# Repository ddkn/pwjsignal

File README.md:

# PWJSignal Daughter Board

This is the daughter board to the [pwjrtos](https://github.com/nanomagneticslab/pwjrtos)
OS. This was built using KiCAD v5.1.5.

These are design files for the PCB; this includes,

* Schematics
* PCB layouts
* Gerbers (for PCB manufacturers)
* Datasheet references

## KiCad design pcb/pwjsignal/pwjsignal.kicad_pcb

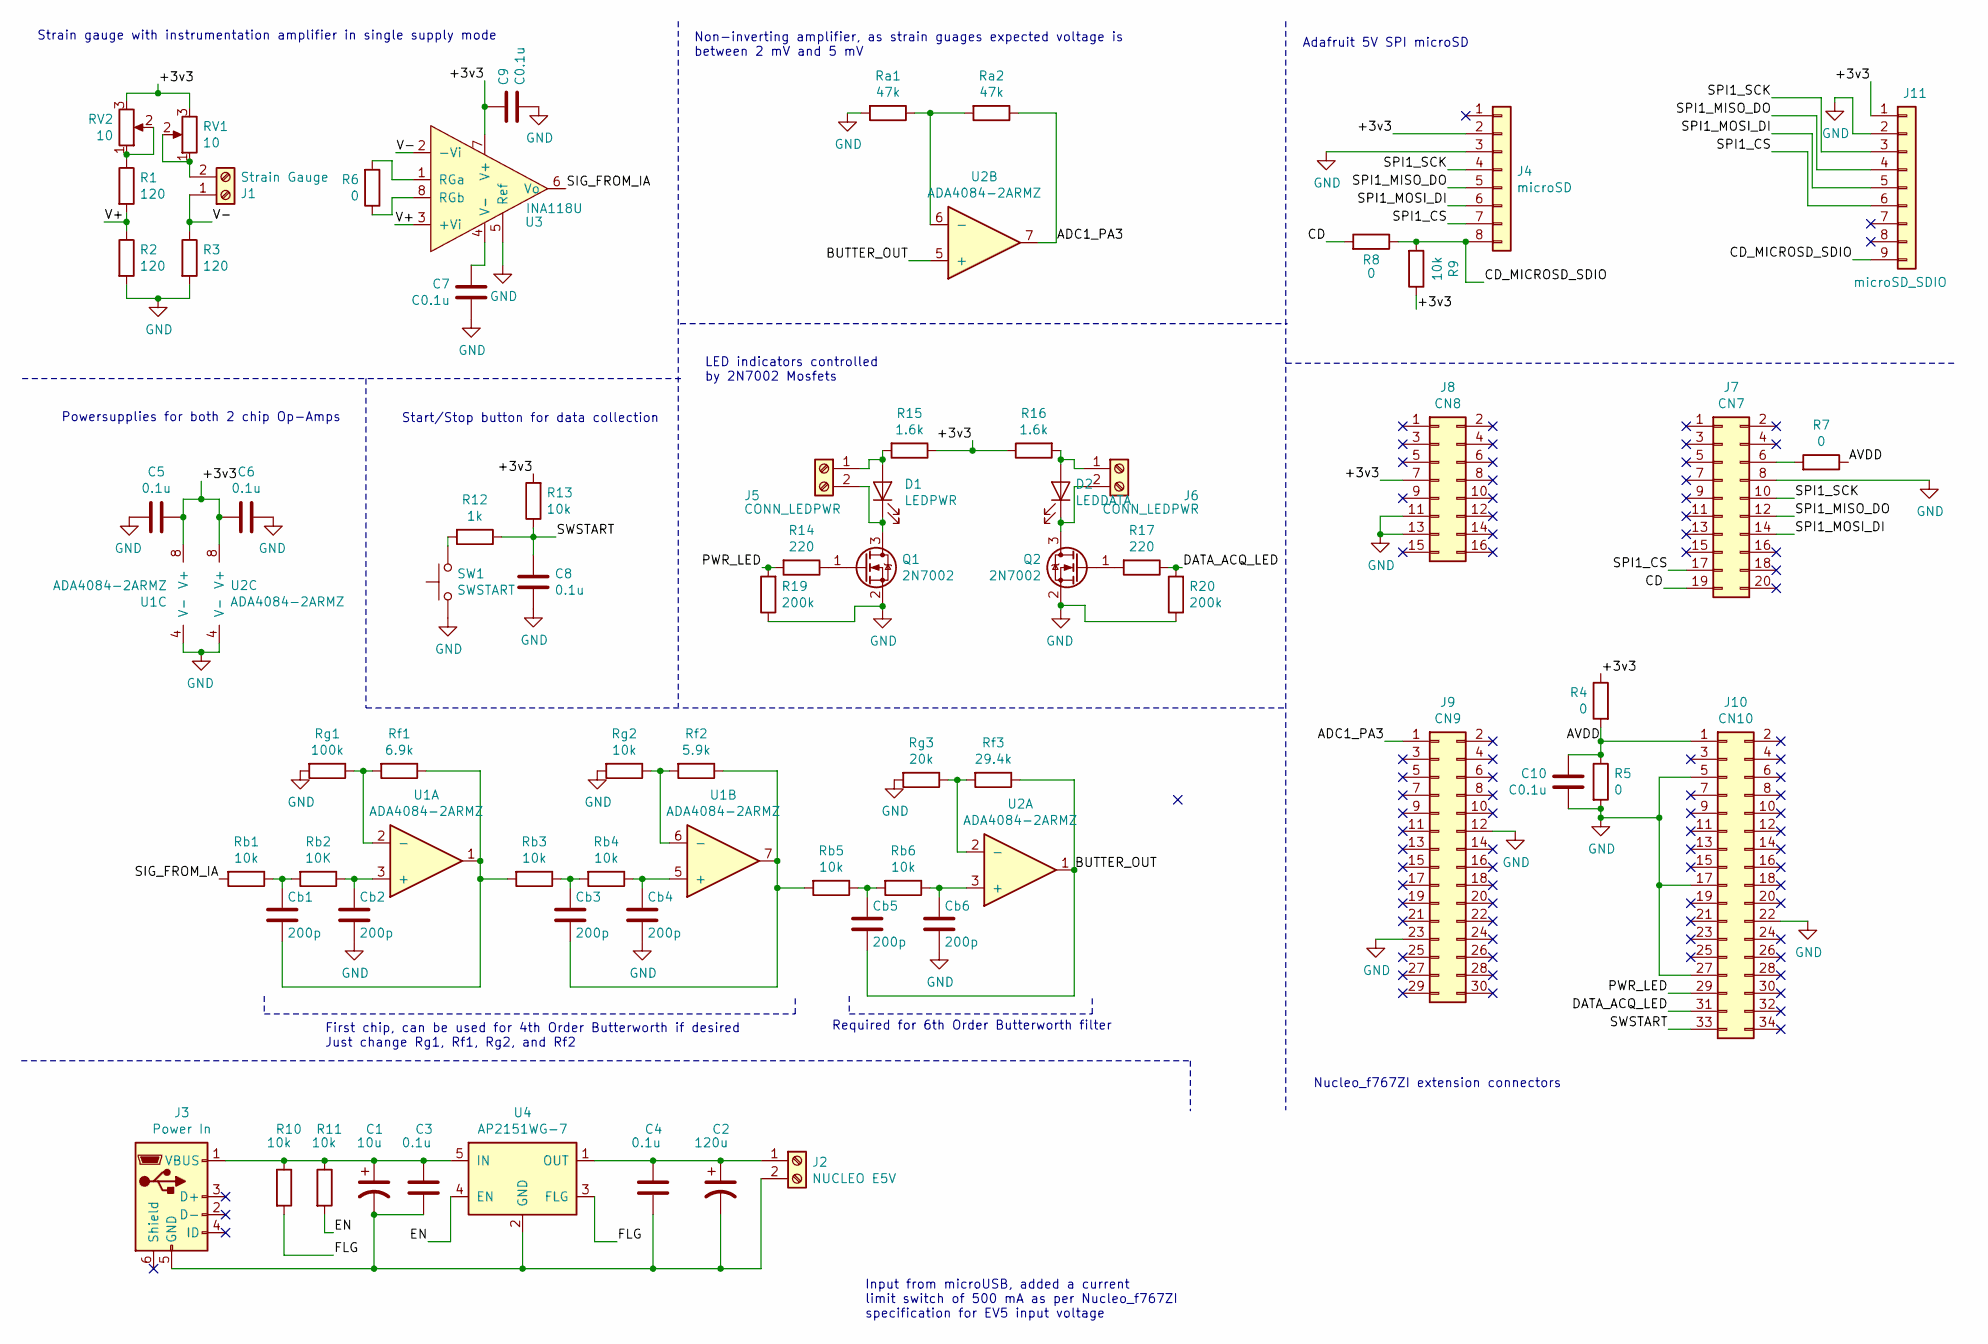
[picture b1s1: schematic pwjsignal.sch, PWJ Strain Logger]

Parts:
C1: 10u; CP_EIA-3216-18_Kemet-A_Pad1.58x1.35mm_HandSolder; MPN TAJA106K006SNJ
C2: 120u; CP_EIA-7343-15_Kemet-W_Pad2.25x2.55mm_HandSolder; MPN 293D127X96R3D2TE3
C3, C4, C5, C6, C8: 0.1u; C_0603_1608Metric_Pad1.05x0.95mm_HandSolder
C7, C10: C0.1u; C_0603_1608Metric_Pad1.05x0.95mm_HandSolder
C9: C0.1u; C_1206_3216Metric_Pad1.42x1.75mm_HandSolder
Cb1, Cb2, Cb3, Cb4, Cb5, Cb6: 200p; C_0603_1608Metric_Pad1.05x0.95mm_HandSolder
D1: LEDPWR; C_0805_2012Metric_Pad1.15x1.40mm_HandSolder; MPN APT2012LVBC/D
D2: LEDDATA; C_0805_2012Metric_Pad1.15x1.40mm_HandSolder; MPN APT2012LSECK/J4-PRV
J1: Strain Gauge; TerminalBlock_TE_282834-2_1x02_P2.54mm_Horizontal; MPN 1546215-2
J2: NUCLEO E5V; TerminalBlock_TE_282834-2_1x02_P2.54mm_Horizontal; MPN 1546215-2
J3: Power In; USB_Micro-B_Amphenol_10103594-0001LF_Horizontal; MPN 10103594-0001LF
J4: microSD; Adafruit_microSD_breakout_Alt; MPN 61300811121
J5, J6: CONN_LEDPWR; TerminalBlock_TE_282834-2_1x02_P2.54mm_Horizontal; MPN 1546215-2
J7: CN7; PinHeader_2x10_P2.54mm_Vertical; MPN 61307221121
J8: CN8; PinHeader_2x08_P2.54mm_Vertical; MPN 61307221121
J9: CN9; PinHeader_2x15_P2.54mm_Vertical; MPN 61307221121
J10: CN10; PinHeader_2x17_P2.54mm_Vertical; MPN 61307221121
J11: microSD_SDIO; Adafruit_microSD_SDIO_breakout
Q1, Q2: 2N7002; SOT-23; MPN 2N7002A-7
R1, R2, R3: 120; R_1206_3216Metric_Pad1.42x1.75mm_HandSolder
R4, R5, R6, R7, R8: 0; R_0603_1608Metric_Pad1.05x0.95mm_HandSolder
R9, R10, R11, R13: 10k; R_0603_1608Metric_Pad1.05x0.95mm_HandSolder
R12: 1k; R_0603_1608Metric_Pad1.05x0.95mm_HandSolder
R14, R17: 220; R_0603_1608Metric_Pad1.05x0.95mm_HandSolder
R15, R16: 1.6k; R_0603_1608Metric_Pad1.05x0.95mm_HandSolder
R19, R20: 200k; R_0603_1608Metric_Pad1.05x0.95mm_HandSolder
RV1, RV2: 10; Potentiometer_Bourns_3214J_Horizontal; MPN PVG3A200C01R00
Ra1, Ra2: 47k; R_0603_1608Metric_Pad1.05x0.95mm_HandSolder
Rb1, Rb3, Rb4, Rb5, Rb6: 10k; R_0603_1608Metric_Pad1.05x0.95mm_HandSolder
Rb2: 10K; R_0603_1608Metric_Pad1.05x0.95mm_HandSolder
Rf1: 6.9k; R_0603_1608Metric_Pad1.05x0.95mm_HandSolder
Rf2: 5.9k; R_0603_1608Metric_Pad1.05x0.95mm_HandSolder
Rf3: 29.4k; R_0603_1608Metric_Pad1.05x0.95mm_HandSolder
Rg1: 100k; R_0603_1608Metric_Pad1.05x0.95mm_HandSolder
Rg2: 10k; R_0603_1608Metric_Pad1.05x0.95mm_HandSolder
Rg3: 20k; R_0603_1608Metric_Pad1.05x0.95mm_HandSolder
SW1: SWSTART; TerminalBlock_TE_282834-2_1x02_P2.54mm_Horizontal
U1, U2: ADA4084-2ARMZ; MSOP-8_3x3mm_P0.65mm; MPN ADA4084-2ARMZ
U3: INA118U; SOIC-8_3.9x4.9mm_P1.27mm
U4: AP2151WG-7; SOT-23-5_HandSoldering; MPN AP2151WG-7

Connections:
/+3v3: C5.1, C6.2, C9.2, J4.2, J8.7, J11.1, R4.1, R9.1, R13.2, R15.1, R16.1, RV1.3, RV2.3, U1.8 (V+), U2.8 (V+), U3.7 (V+)
/ADC1_PA3: J9.1, Ra2.1, U2.7
/AVDD: C10.2, J10.1, R4.2, R5.1, R7.1
/BUTTER_OUT: Cb5.2, Rf3.1, U2.1, U2.5 (+)
/CD: J7.19, R8.2
/CD_MICROSD_SDIO: J4.8, J11.9, R8.1, R9.2
/DATA_ACQ_LED: J10.31, R17.1, R20.2
/EN: R11.2, U4.4 (EN)
/FLG: R10.2, U4.3 (FLG)
/PWR_LED: J10.29, R14.2, R19.2
/SIG_FROM_IA: Rb1.2, U3.6 (Vo)
/SPI1_CS: J4.7, J7.17, J11.6
/SPI1_MISO_DO: J4.5, J7.12, J11.4
/SPI1_MOSI_DI: J4.6, J7.14, J11.5
/SPI1_SCK: J4.4, J7.10, J11.3
/SWSTART: C8.1, J10.33, R12.1, R13.1
/V+: R1.2, R2.1, U3.3 (+Vi)
/V-: J1.1, R3.1, U3.2 (-Vi)
GND: C5.2, C6.1, C7.1, C8.2, C9.1, C10.1, Cb2.2, Cb4.2, Cb6.2, J4.3, J7.8, J8.11, J8.13, J9.12, J9.23, J10.5, J10.17, J10.22, J10.27, J11.2, Q1.2 (S), Q2.2 (S), R2.2, R3.2, R5.2, R19.1, R20.1, Ra1.2, Rg1.2, Rg2.2, Rg3.2, SW1.1, U1.4 (V-), U2.4 (V-), U3.5 (Ref)
unnamed: C1.1, C3.1, J3.1 (VBUS), R10.1, R11.1, U4.5 (IN)
unnamed: C1.2, C2.2, C3.2, C4.2, J2.2, J3.5 (GND), U4.2 (GND)
unnamed: C2.1, C4.1, J2.1, U4.1 (OUT)
unnamed: C7.2, U3.4 (V-)
unnamed: Cb1.1, Rb1.1, Rb2.2
unnamed: Cb1.2, Rb3.2, Rf1.1, U1.1
unnamed: Cb2.1, Rb2.1, U1.3 (+)
unnamed: Cb3.1, Rb3.1, Rb4.2
unnamed: Cb3.2, Rb5.2, Rf2.1, U1.7
unnamed: Cb4.1, Rb4.1, U1.5 (+)
unnamed: Cb5.1, Rb5.1, Rb6.2
unnamed: Cb6.1, Rb6.1, U2.3 (+)
unnamed: D1.1 (K), J5.2, Q1.3 (D)
unnamed: D1.2 (A), J5.1, R15.2
unnamed: D2.1 (K), J6.2, Q2.3 (D)
unnamed: D2.2 (A), J6.1, R16.2
unnamed: J1.2, RV1.1, RV1.2
unnamed: J7.6, R7.2
unnamed: Q1.1 (G), R14.1
unnamed: Q2.1 (G), R17.2
unnamed: R1.1, RV2.1, RV2.2
unnamed: R6.1, U3.8 (RGb)
unnamed: R6.2, U3.1 (RGa)
unnamed: R12.2, SW1.2
unnamed: Ra1.1, Ra2.2, U2.6 (-)
unnamed: Rf1.2, Rg1.1, U1.2 (-)
unnamed: Rf2.2, Rg2.1, U1.6 (-)
unnamed: Rf3.2, Rg3.1, U2.2 (-)

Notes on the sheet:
Input from microUSB, added a current limit switch of 500 mA as per Nucleo_f767ZI specification for EV5 input voltage
Adafruit 5V SPI microSD
Nucleo_f767ZI extension connectors
Strain gauge with instrumentation amplifier in single supply mode
Non-inverting amplifier, as strain guages expected voltage is between 2 mV and 5 mV
First chip, can be used for 4th Order Butterworth if desired Just change Rg1, Rf1, Rg2, and Rf2
Required for 6th Order Butterworth filter
Powersupplies for both 2 chip Op-Amps
Start/Stop button for data collection
LED indicators controlled by 2N7002 Mosfets

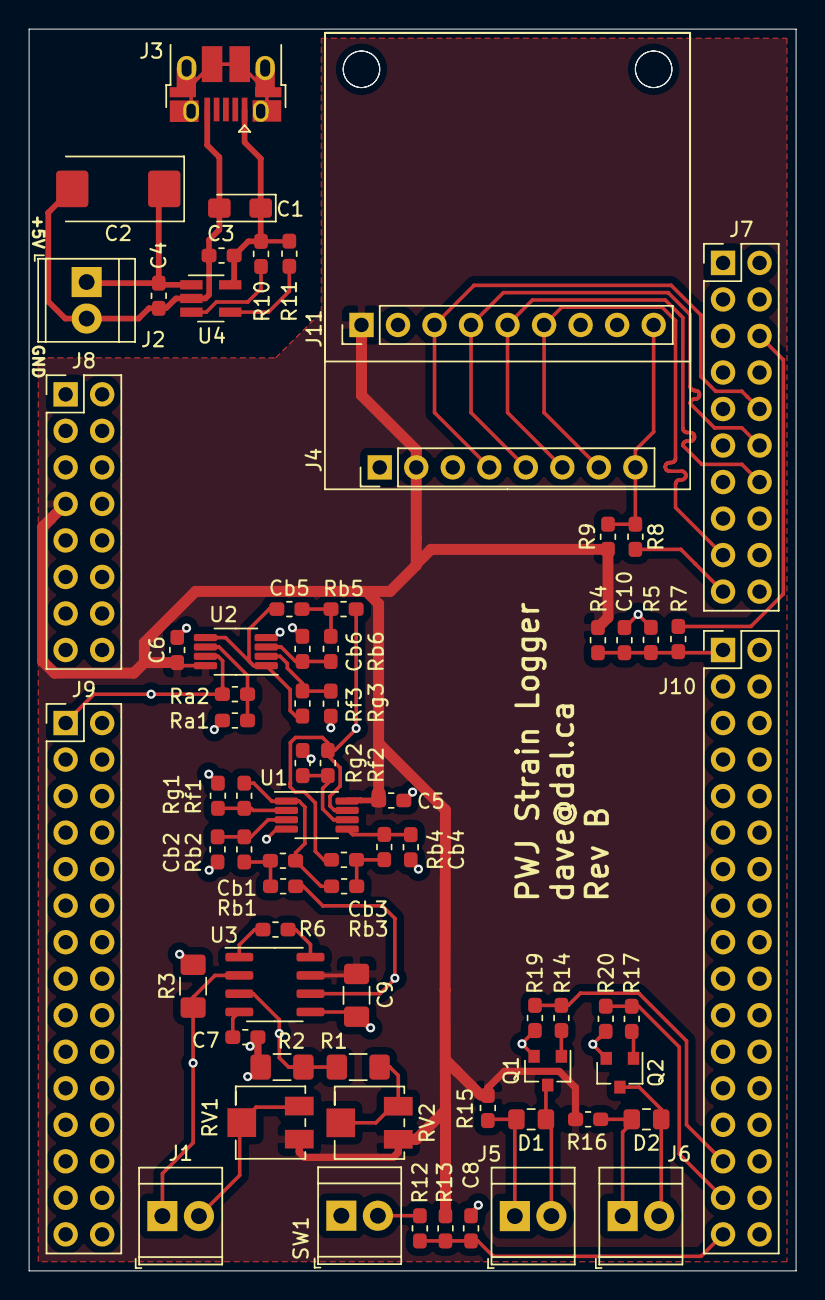
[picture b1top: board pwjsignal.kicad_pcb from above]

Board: 2 copper layers, 53.3 x 86.4 mm, 71 parts (0 on the bottom side), 47 nets.

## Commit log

2021-05-15 Initial commit of Rev. A of pwjsignal daughter board
2021-05-15 Add README.md
2021-06-24 Added Rev B of board with updated filters
    * This includes new Low Pass filter cutoff frequency 80kHz.
    * New instrumentation amplifier for low noise
    * Added test points
2021-06-24 Added new component references
